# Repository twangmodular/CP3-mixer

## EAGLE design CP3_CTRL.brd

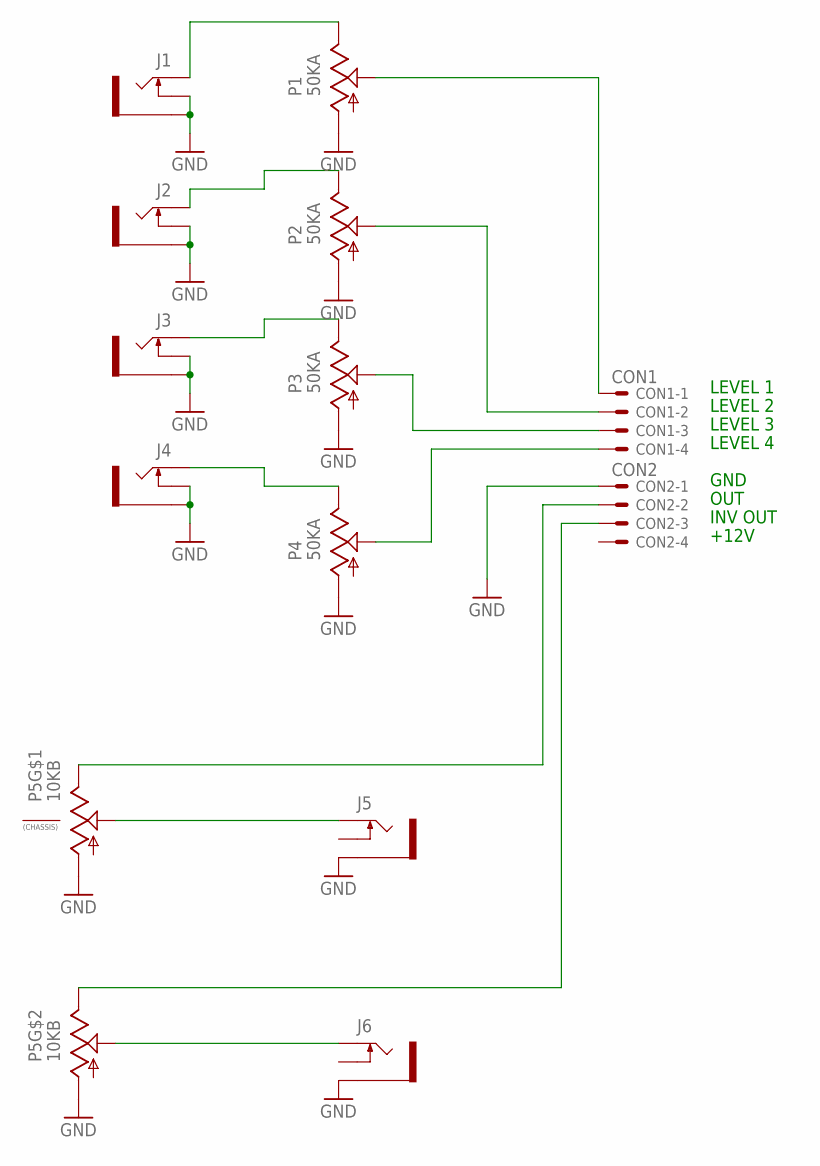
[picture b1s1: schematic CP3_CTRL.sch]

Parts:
CON1: CON1; 22-23-2041
CON2: CON2; 22-23-2041
J1, J2, J3, J4, J5, J6: WQP518MA; WQP-PJ301M-12_JACK
P1, P2, P3, P4: 50KA; 9MM_SNAP-IN_POT
P5: 10KB; DUAL_9MM_SNAP-IN_POT

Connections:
GND: CON2.1, J1.P$2_SWITCH (SWITCH), J1.P$3_SLEEVE (SLEEVE), J2.P$2_SWITCH (SWITCH), J2.P$3_SLEEVE (SLEEVE), J3.P$2_SWITCH (SWITCH), J3.P$3_SLEEVE (SLEEVE), J4.P$2_SWITCH (SWITCH), J4.P$3_SLEEVE (SLEEVE), J5.P$3_SLEEVE (SLEEVE), J6.P$3_SLEEVE (SLEEVE), P1.1 (A), P2.1 (A), P3.1 (A), P4.1 (A), P5.1 (A), P5.1B (A)
unnamed: J1.P$1_TIP (TIP), P1.3 (E)
unnamed: CON1.1, P1.2 (S)
unnamed: CON1.2, P2.2 (S)
unnamed: CON1.3, P3.2 (S)
unnamed: CON1.4, P4.2 (S)
unnamed: J2.P$1_TIP (TIP), P2.3 (E)
unnamed: J3.P$1_TIP (TIP), P3.3 (E)
unnamed: J4.P$1_TIP (TIP), P4.3 (E)
unnamed: CON2.2, P5.3 (E)
unnamed: CON2.3, P5.3B (E)
unnamed: J5.P$1_TIP (TIP), P5.2 (S)
unnamed: J6.P$1_TIP (TIP), P5.2B (S)

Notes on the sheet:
LEVEL 1
LEVEL 2
LEVEL 3
LEVEL 4
GND
OUT
INV OUT
+12V

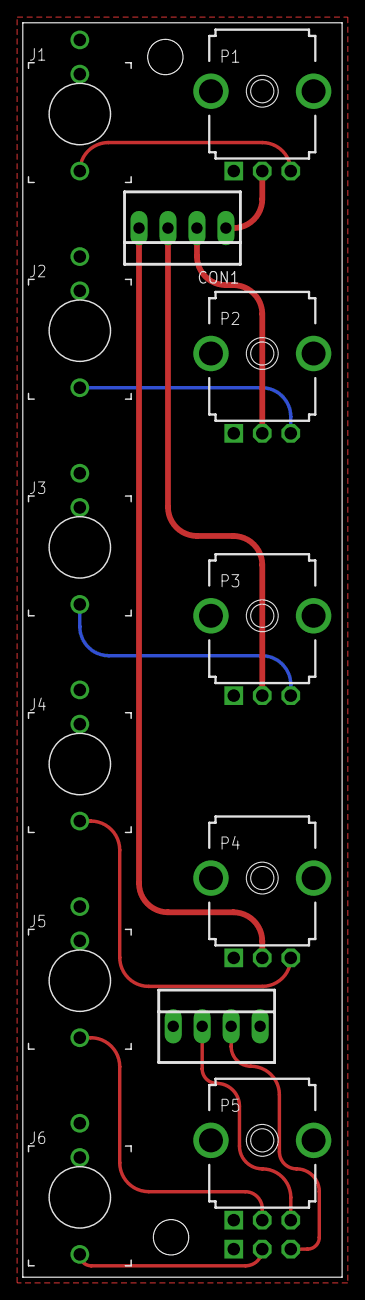
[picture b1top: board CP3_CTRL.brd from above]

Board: 2 copper layers, 28.0 x 110.0 mm, 13 parts (0 on the bottom side), 13 nets.

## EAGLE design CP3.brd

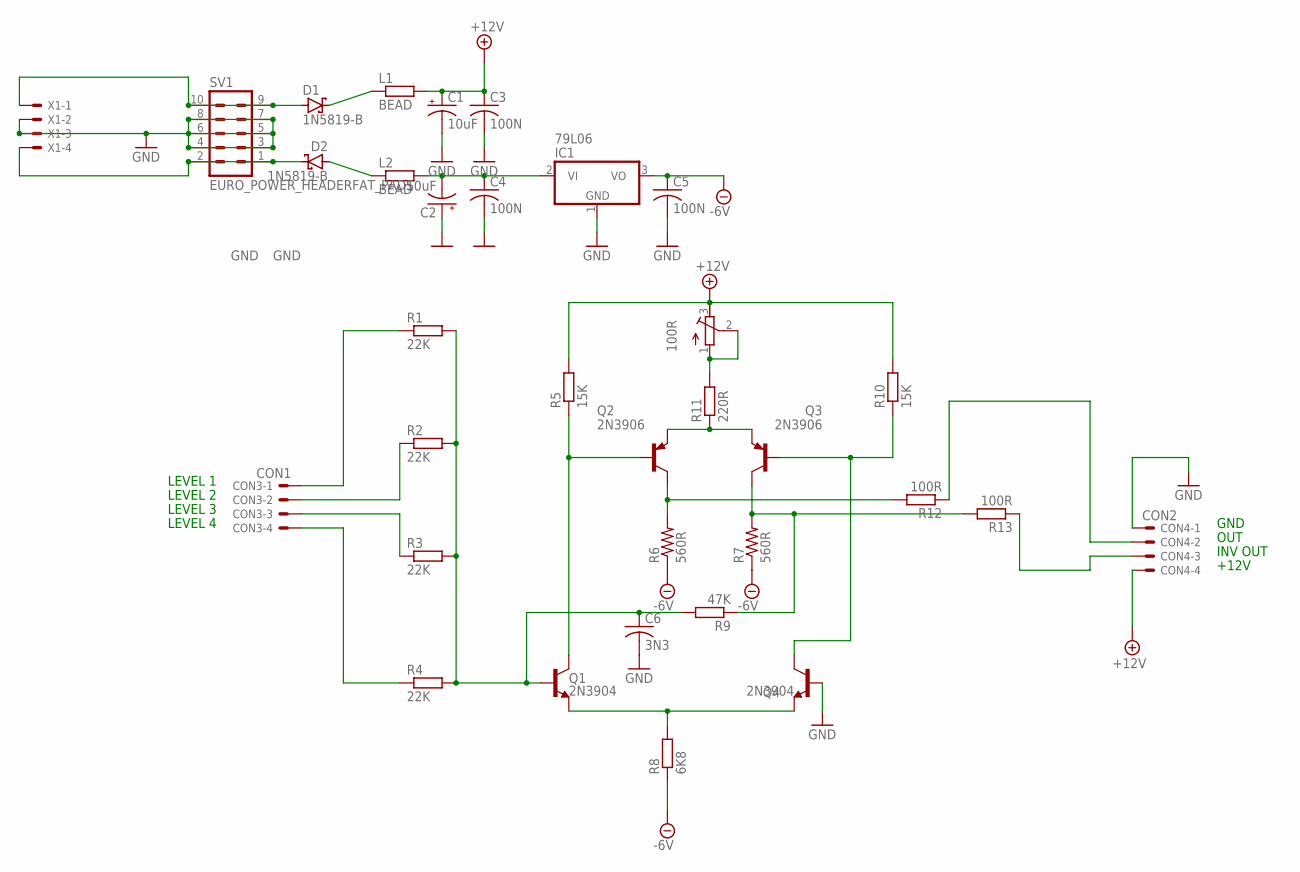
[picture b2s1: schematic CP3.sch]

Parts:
100R: R-TRIMM3296W; RTRIM3296W
C1, C2: 10uF; E2,5-7
C3, C4, C5: 100N; C025-025X050
C6: 3N3; C025-025X050
CON3: CON1; 22-23-2041
CON4: CON2; 22-23-2041
D1, D2: 1N5819-B; DO41-7.6
IC1: 79L06; TO92
L1, L2: BEAD; 10MM_RESISTOR
Q1, Q4: 2N3904; TO-92
Q2, Q3: 2N3906; TO92
R1, R2, R3, R4: 22K; 10MM_RESISTOR
R5, R10: 15K; 10MM_RESISTOR
R6, R7: 560R; 0207/12
R8: 6K8; 10MM_RESISTOR
R9: 47K; 10MM_RESISTOR
R11: 220R; 10MM_RESISTOR
R12, R13: 100R; 10MM_RESISTOR
SV1: EURO_POWER_HEADERFAT_PADS; EURO_PWR_HEADER_FAT
X1: KK-156-4

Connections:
+12V: 100R.3 (E), C1.+, C3.1, CON4.4, L1.2, R5.2, R10.2
-5V: C5.1, IC1.3 (VO), R6.1, R7.1, R8.1
GND: C1.-, C2.+, C3.2, C4.2, C5.2, C6.2, CON4.1, IC1.1 (GND), Q4.2 (B), SV1.3, SV1.4, SV1.5, SV1.6, SV1.7, SV1.8, X1.2, X1.3
unnamed: D1.A, SV1.9, SV1.10, X1.1
unnamed: D1.C, L1.1
unnamed: D2.C, SV1.1, SV1.2, X1.4
unnamed: D2.A, L2.1
unnamed: C2.-, C4.1, IC1.2 (VI), L2.2
unnamed: CON3.1, R1.1
unnamed: CON3.2, R2.1
unnamed: CON3.3, R3.1
unnamed: CON3.4, R4.1
unnamed: C6.1, Q1.2 (B), R1.2, R2.2, R3.2, R4.2, R9.2
unnamed: Q1.1 (E), Q4.1 (E), R8.2
unnamed: Q1.3 (C), Q2.2 (B), R5.1
unnamed: Q2.1 (C), R6.2, R12.2
unnamed: Q3.1 (C), R7.2, R9.1, R13.2
unnamed: Q2.3 (E), Q3.3 (E), R11.1
unnamed: 100R.1 (A), 100R.2 (S), R11.2
unnamed: CON4.3, R13.1
unnamed: Q3.2 (B), Q4.3 (C), R10.1
unnamed: CON4.2, R12.1

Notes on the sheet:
LEVEL 1
LEVEL 2
LEVEL 3
LEVEL 4
GND
OUT
INV OUT
+12V

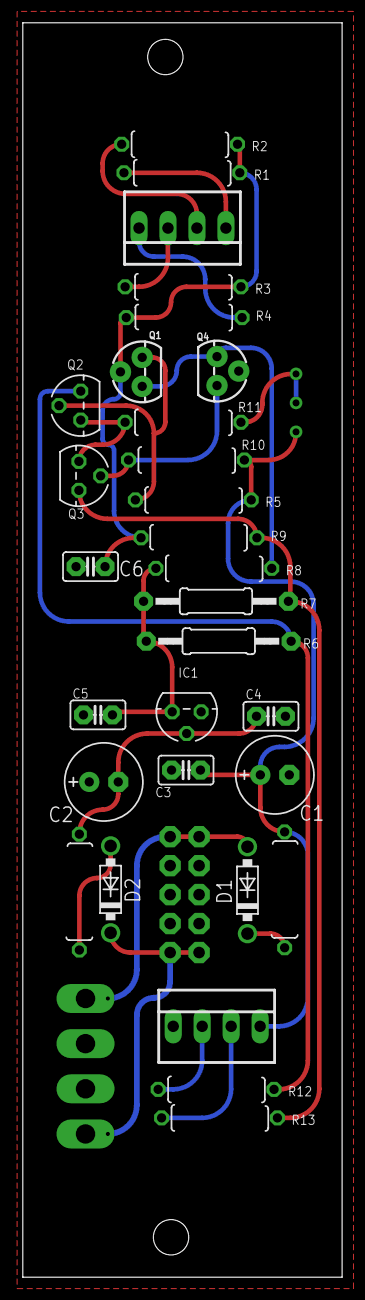
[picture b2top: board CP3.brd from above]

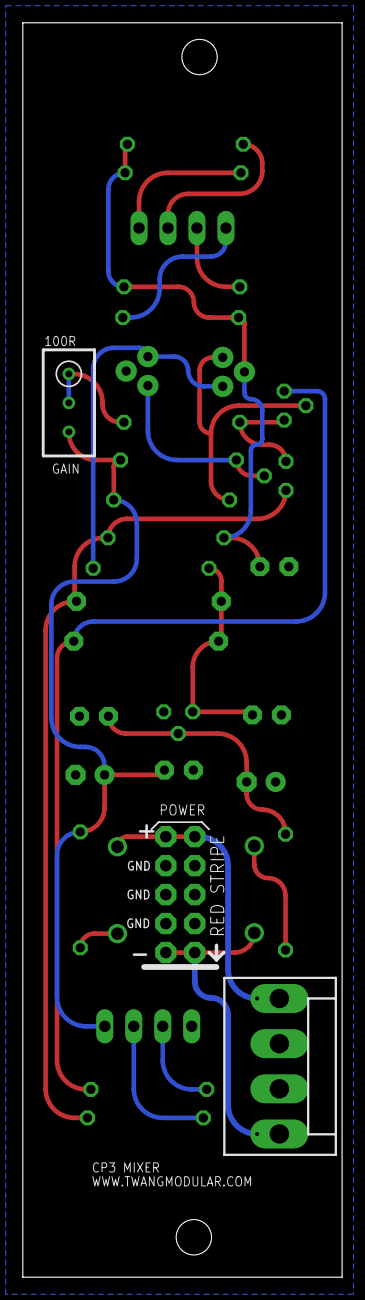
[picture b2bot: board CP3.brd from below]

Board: 2 copper layers, 28.0 x 110.0 mm, 33 parts (3 on the bottom side), 22 nets.

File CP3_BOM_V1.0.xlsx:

Index | Qty | Description | Specs | Value | Package | References
MAIN PCB
C1, C2 | 2 | Polarized capacitor | >=25V | 10uF
C3, C4, C5 | 3 | Ceramic capacitor |  | 100nF
C6 | 1 | Film capacitor |  | 3.3nF
R12, R13 | 2 | Resistor | 1/4W | 100R
R5, R10 | 2 | Resistor | 1/4W | 15K
R11 | 1 | Resistor | 1/4W | 220R
R1, R2, R3, R4 | 4 | Resistor | 1/4W | 22K
R9 | 1 | Resistor | 1/4W | 47K
R6, R7 | 2 | Resistor | 1/2W | 560R
R8 | 1 | Resistor | 1/4W | 6.8K
L1, L2 | 2 | Ferrite bead |  | 10R
Q1, Q4 | 2 | NPN transistor |  | 2n3904 | TO-92
Q2, Q3 | 2 | PNP transistor |  | 2n3906 | TO-92
IC1 | 1 | Voltage regulator |  | 79L06 | TO-92
D1, D2 | 2 | Diode |  | 1n5819 | DO-41
Trimpot | 1 |  |  | 100R | 3296W
CONN1, CONN2 | 2 | Connector male | 2.54mm | 4 pin
CONN1, CONN2 | 2 | Connector feemale | 2.54mm | 4 pin
CONTROL PCB
P1, P2, P3, P4 | 4 | Potentiometer | 9mm | A50K
P5 | 1 | Dual gang potentiometer | 9mm | B50K
J1-J6 | 6 | Mono jack socket |  | WQP518MA |  | https://twangmodular.ru/product/3-5mm-jack/

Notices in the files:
parts and their libraries:
SparkFun-DiscreteSemi: Licensing: Creative Commons ShareAlike 4.0 International - https://creativecommons.org/licenses/by-sa/4.0
